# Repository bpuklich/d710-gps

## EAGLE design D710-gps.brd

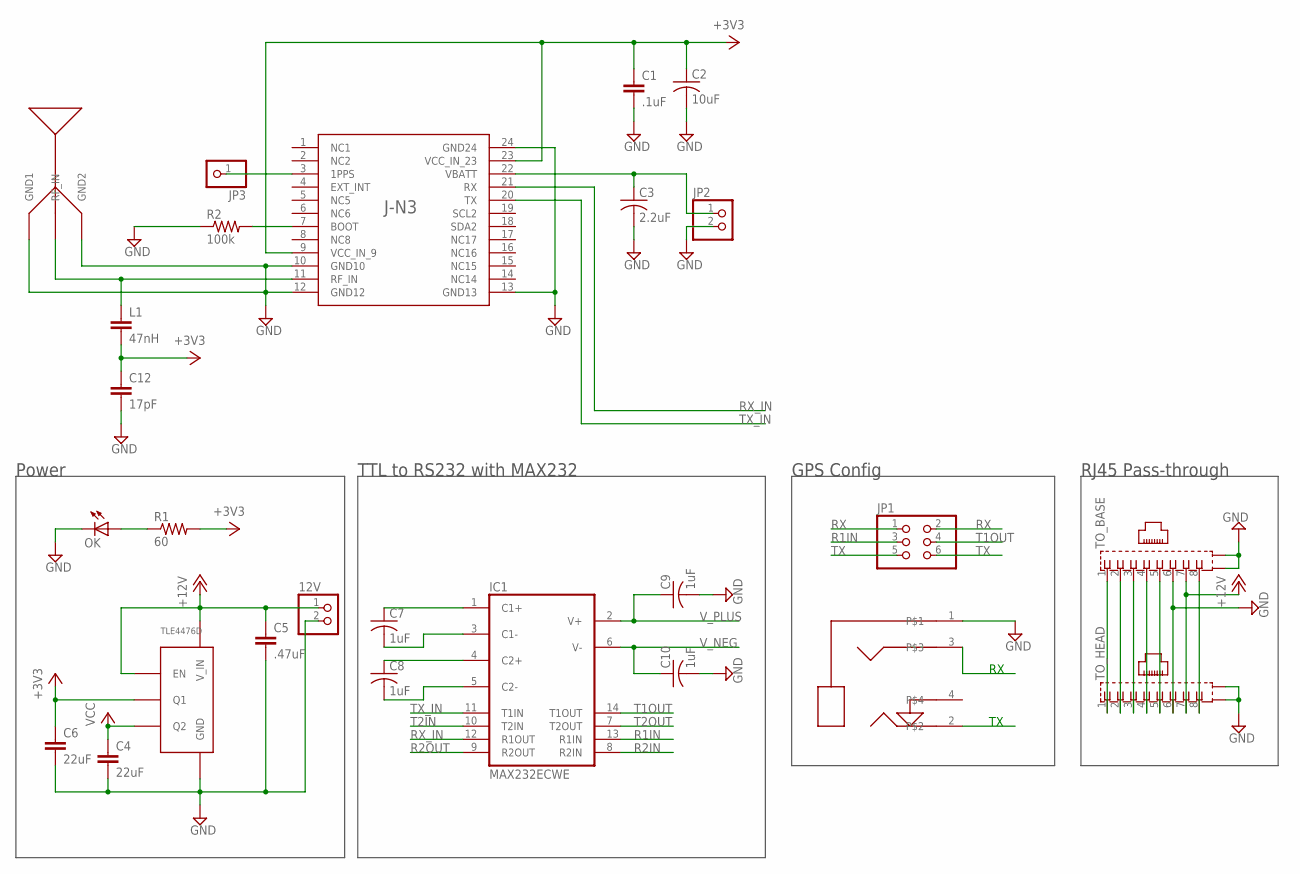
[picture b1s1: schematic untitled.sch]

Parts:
12V: PINHD-1X2; 1X02
ANT: GEO_HELIX_GPSANT
C1: .1uF; C0805
C2: 10uF; C0805; MPN 06034D106MAT2A
C3: 2.2uF; C0805
C4, C6: 22uF; C0805
C5: .47uF; C0805
C7, C8, C9, C10: 1uF; C0805; MPN 02016D105MAT2A
C12: 17pF; C0603
GPS: 2.5MM_JACK; 2.5MM_AUDIO
IC1: MAX232ECWE; SO16L
JP1: PINHD-2X3; 2X03
JP2: PINHD-1X2; 1X02
JP3: PINHD-1X1; 1X01
L1: 47nH; C0603
OK: LEDCHIPLED_0805; CHIPLED_0805
R1: 60; R0805
R2: 100k; R0603
TLE4476D: TLE4476D; TO-252-5
TO_BASE: 555141-1; 555153-1
TO_HEAD: 555141-1; 555153-1
U$1: TELIT_JN3; 24-SMD

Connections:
+3V3: C1.1, C2.1, C6.1, C12.1, L1.2, R1.2, TLE4476D.Q1, U$1.9 (VCC_IN_9), U$1.23 (VCC_IN_23)
+5V: C4.1, IC1.16 (VCC), TLE4476D.Q2
+12V: 12V.1, C5.1, TLE4476D.EN, TLE4476D.V_IN, TO_BASE.7, TO_HEAD.7
GND: 12V.2, ANT.GND1, ANT.GND2, C1.2, C2.2, C3.2, C4.2, C5.2, C6.2, C9.2, C10.2, C12.2, GPS.1, IC1.15 (GND), JP2.2, OK.C, R2.1, TLE4476D.GND, TO_BASE.6, TO_BASE.G1 (S1), TO_BASE.G2 (S2), TO_HEAD.6, TO_HEAD.G1 (S1), TO_HEAD.G2 (S2), U$1.10 (GND10), U$1.12 (GND12), U$1.13 (GND13), U$1.24 (GND24)
unnamed: ANT.RF_IN, L1.1, U$1.11 (RF_IN)
unnamed: OK.A, R1.1
unnamed: R2.2, U$1.7 (BOOT)
unnamed: C3.1, JP2.1, U$1.22 (VBATT)
unnamed: JP3.1, U$1.3 (1PPS)
unnamed: C7.1, IC1.1 (C1+)
unnamed: C7.2, IC1.3 (C1-)
unnamed: C8.1, IC1.4 (C2+)
unnamed: C8.2, IC1.5 (C2-)
unnamed: TO_BASE.1, TO_HEAD.1
unnamed: TO_BASE.2, TO_HEAD.2
unnamed: TO_BASE.3, TO_HEAD.3
unnamed: TO_BASE.4, TO_HEAD.4
unnamed: TO_BASE.5, TO_HEAD.5
unnamed: TO_BASE.8, TO_HEAD.8
R1IN: IC1.13 (R1IN), JP1.3
R2IN: IC1.8 (R2IN)
R2OUT: IC1.9 (R2OUT)
RX: GPS.3, JP1.1, JP1.2
RX_IN: IC1.12 (R1OUT), U$1.21 (RX)
T1OUT: IC1.14 (T1OUT), JP1.4
T2IN: IC1.10 (T2IN)
T2OUT: IC1.7 (T2OUT)
TX: GPS.2, JP1.5, JP1.6
TX_IN: IC1.11 (T1IN), U$1.20 (TX)
V_NEG: C10.1, IC1.6 (V-)
V_PLUS: C9.1, IC1.2 (V+)

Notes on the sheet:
GPS Config
RJ45 Pass-through
Power
TTL to RS232 with MAX232

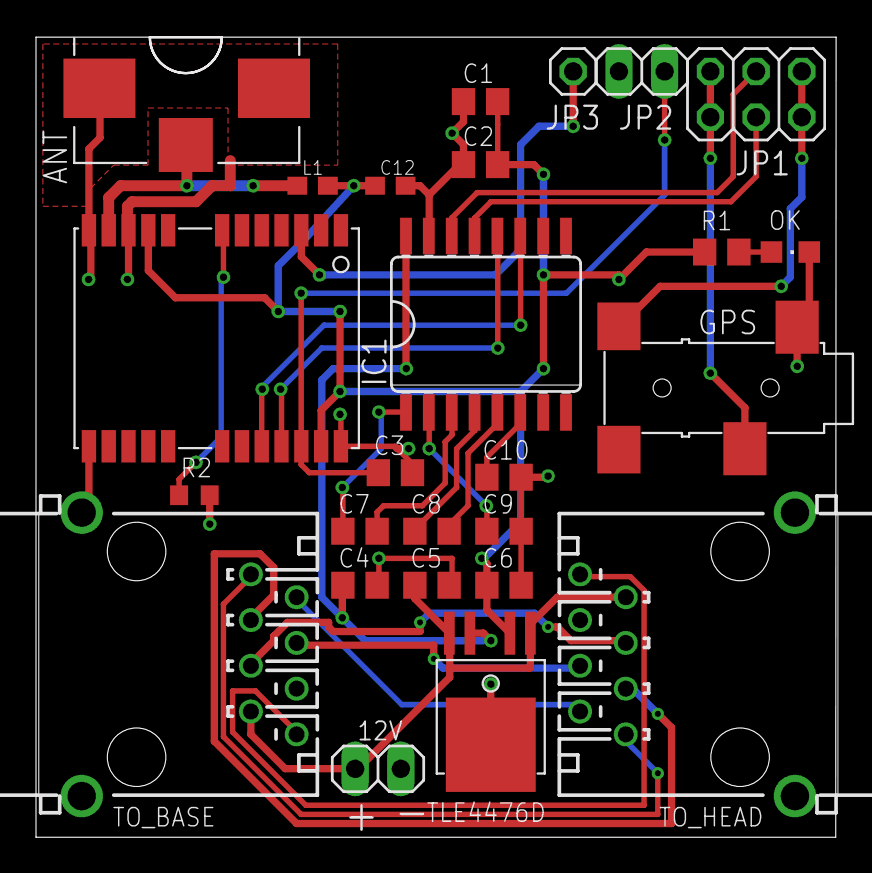
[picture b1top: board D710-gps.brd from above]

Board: 2 copper layers, 44.5 x 44.5 mm, 26 parts (0 on the bottom side), 27 nets.

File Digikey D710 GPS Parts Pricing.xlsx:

Part # | Part | How many / board | $ Per 1 | $ Per 10 | $ Per 100 | $ Per 1000
 |  |  | 1 | 10 | 100 | 1000
943-1016-1-ND | JN3 GPS Module | 1 | 19.17 | 16.43 | 14.375 | 14.375
TLE4476DCT-ND | IC REG TLE4476D | 1 | 3.32 | 2.985 | 2.4325 | 1.65855
1276-2910-1-ND | Cap Ceramic 22uF 10V | 2 | 0.4 | 0.346 | 0.173 | 0.11371
1276-1074-1-ND | Cap Ceramic .47uF 25V | 1 | 0.12 | 0.084 | 0.0385 | 0.021
1276-1007-1-ND | Cap Ceramic .1uF 50V | 1 | 0.1 | 0.031 | 0.0141 | 0.00768
1276-2893-1-ND | Cap Ceramic 10uF 16V | 1 | 0.2 | 0.137 | 0.0696 | 0.04228
1276-2953-1-ND | Cap Ceramic 2.2uF 25V | 1 | 0.16 | 0.11 | 0.0523 | 0.03031
P62ADCT-ND | Res 62 Ohm 1/4W | 1 | 0.23 | 0.0874 | 0.0665 | 0.02432
P100KGCT-ND | Res 100 Ohm 1/10W | 2 | 0.1 | 0.0092 | 0.007 | 0.00256
160-1423-1-ND | LED Green 0805 | 1 | 0.32 | 0.248 | 0.135 | 0.0585
CP-2524SJCT-ND | Conn Audio Jack 2.5mm | 1 | 1.28 | 0.998 | 0.7614 | 0.4912
A31437-ND | Conn RJ45 | 2 | 2.02 | 1.832 | 1.5707 | 1.12193
MAX232ECWE+-ND | MAX232ECWE | 1 | 4.88 | 4.636 | 2.36 | 2.07826
311-1457-1-ND | Cap Ceramic 1uF 16V | 4 | 0.1 | 0.044 | 0.0202 | 0.01101
D710GPSv2 | 2-layer PCB Board made | 1 | 6 | 6 | 6 | 6
SL1204R | Quadrifilar geo helix GPS antenna | 1 | 19 | 19 | 19 | 19
490-2631-1-ND | INDUCTOR 47NH 200MA 0402 | 1 | 0.1 | 0.064 | 0.0448 | 0.03328
490-5868-1-ND | CAP CER 22PF 50V 5% NP0 0402 | 1 | 0.1 | 0.021 | 0.0096 | 0.00525
 |  | Cost Per 1 | 62.02
 |  | Cost Per 10 |  | 55.3818
 |  | Cost Per 100 |  |  | 48.9415
 |  | Cost Per 1000 |  |  |  | 46.34607
 |  | Total investment cost | 62.02 | 553.818 | 4894.15 | 46346.07
 |  | Profit if sold @ $50 | -12.02 | -53.818 | 105.849999999999 | 3653.93
 |  | Profit if sold @ $60 | -2.02000000000001 | 46.182 | 1105.85 | 13653.93
 |  | Profit if sold @ $70 | 7.97999999999999 | 146.182 | 2105.85 | 23653.93
 |  | Profit if sold @ $80 | 17.98 | 246.182 | 3105.85 | 33653.93
 |  | Profit if sold @ $90 | 27.98 | 346.182 | 4105.85 | 43653.93
 |  | Profit if sold @ $100 | 37.98 | 446.182 | 5105.85 | 53653.93
Geo Helix | http://www.richardsonrfpd.com/Pages/Search-Results.aspx?prod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
 | http://www.richardsonrfpd.com/Pages/Product-Details.aspx?pro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
http://www.vetco.net/catalog/product_info.php?products_id=7679

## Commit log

2014-01-22 Adding initial files
2014-01-22 Renamed files
2014-01-22 Added parts file. Parts not contained within this file should be in the default eagle cad library directory.
2014-01-22 Added images of the actual completed board and renderings of the PCB
2014-02-05 Added Parts list
